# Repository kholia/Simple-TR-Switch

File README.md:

### Simple-TR-Switch

This is a non-RF-sensing, MCU PTT-controlled `Simple T/R Switch` with RX
Grounding feature which can be built for less than 2 dollars!

It was designed, and tested for https://github.com/kholia/Easy-Transceiver project.

#### Various approaches

TX power is 10W from IC-705 operating in FM mode.

- With a 2-channel relay as a T/R switch, when both RX Ground and Center are
  disconnected and left floating, a voltage of around ~2.2v is induced across
  RX connections which is unsafe for typical SDRs.

  ~2.2 Vpp is 10.93 dBm!

  https://www.random-science-tools.com/electronics/dBm-Watts-volts.htm

- With a 1-channel relay as a T/R switch which is switching the `Center`
  connection only, and with all Grounds (TX, RX, Antenna) shorted, a voltage of
  around ~1.66v is induced across RX connections which is theoretically safe
  for common SDRs.

- With a 2-channel relay as a T/R switch, with all Grounds (TX, RX, Antenna)
  shorted, with `Center` switching using Channel 1, and RX Center Grounding
  using Channel 2 during TX, a voltage of around ~500mV is induced across RX
  connections which should be fine for most common SDRs.

#### Comparisons

No external 12v power is needed unlike `Easy TR Switch` from https://www.qrpkits.com/ezseries.html.

The ~4000 INR `SDR Transceiver and Receiver Switch Antenna Sharer TR Switch Box
160 MHz` from Banggood doesn't work in `Automatic Mode` if there is
`Broadcast/SW Interference` in your area. The Banggood TR switch switches on
the RTX (red) and disconnects the SDR (RX) as soon as the antenna is connected
under `BCI` conditions, when operating in `Automatic Mode`.

#### BOM

- 5V 2A DPDT OEN MICRO RELAY 46-05-2C

  - https://etstore.in/index.php/product/oen-micro-relay-5v-dpdt-46-05-2c/
  - https://www.tomsonelectronics.com/products/oen-signal-relay-5v-dpdt

#### Added Protection

Here is another additional mechanism to protect sensitive SDRs.

This is OK for HF (shortwave).

#### Alternate (but riskier) Option

Solid switching using BS170 could be another option.

The [info](./info) folder has more information on this.

#### Credits

Thanks to VU2ASH (Ashok Joshi), K.P.S. Kang, and LW1ECP (Daniel Alonso) for all
the help.

https://circuits-diy.com/optocoupler-relay-driver-with-pc817-2n3904/

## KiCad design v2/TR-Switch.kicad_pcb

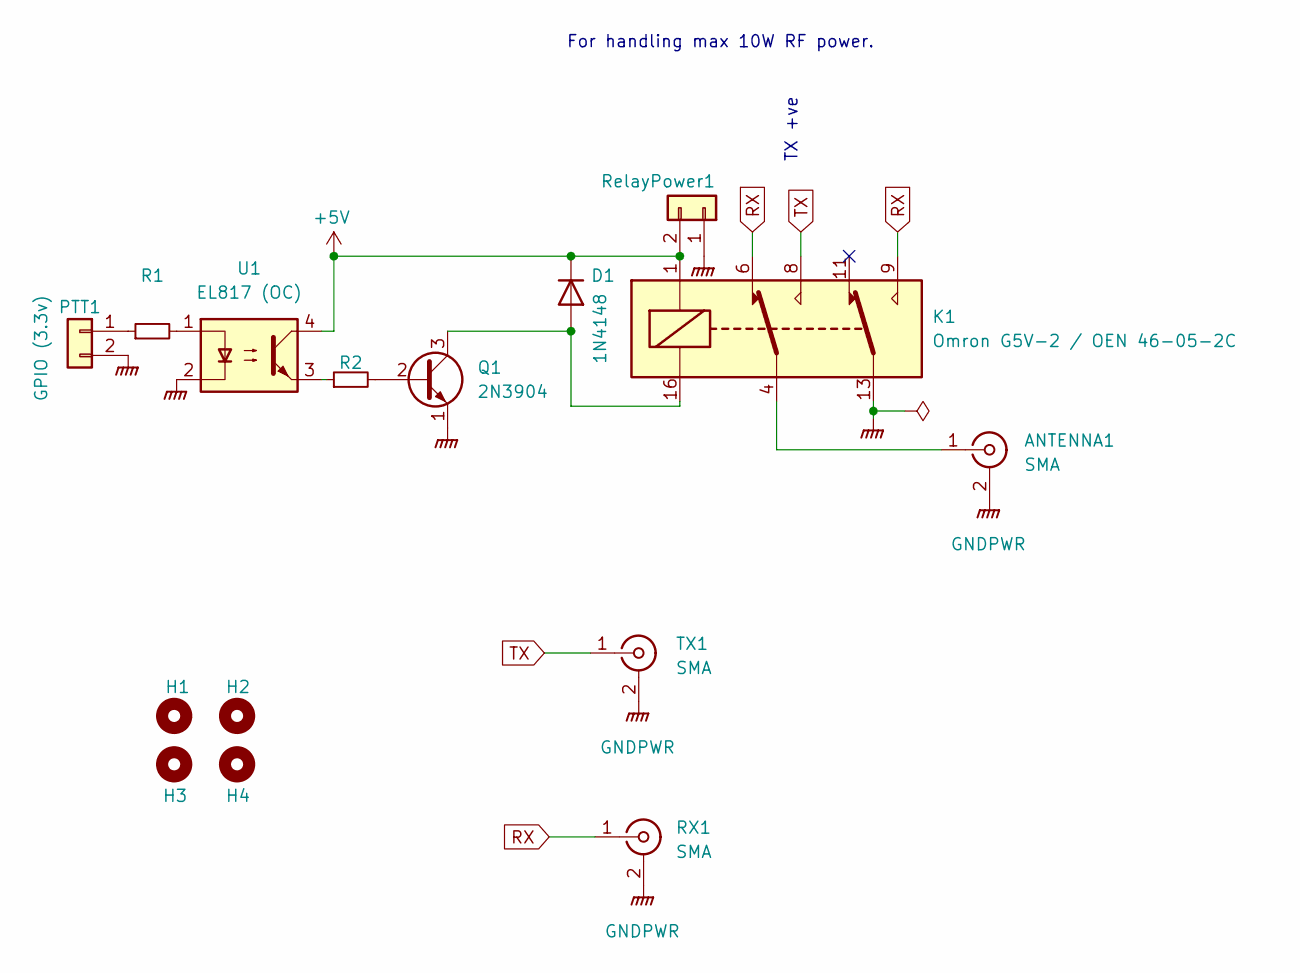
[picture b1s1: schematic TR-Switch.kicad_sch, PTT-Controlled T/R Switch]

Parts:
ANTENNA1: SMA; SMA_Amphenol_901-144_Vertical
D1: 1N4148; D_DO-35_SOD27_P2.54mm_Vertical_KathodeUp
H1, H2, H3, H4: MountingHole; MountingHole_2.2mm_M2
K1: Omron G5V-2 / OEN 46-05-2C; Relay_DPDT_Omron_G5V-2
PTT1: GPIO (3.3v); PinHeader_1x02_P2.54mm_Vertical
Q1: 2N3904; PinSocket_1x03_P2.54mm_Vertical
R1, R2: R_1206_3216Metric_Pad1.30x1.75mm_HandSolder
RELAY_POWER1: RelayPower1; PinHeader_1x02_P2.54mm_Vertical
RX1: SMA; SMA_Amphenol_901-144_Vertical
TX1: SMA; SMA_Amphenol_901-144_Vertical
U1: EL817 (OC); DIP-4_W7.62mm

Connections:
+5V: D1.1 (K), K1.1, RELAY_POWER1.2, U1.4
GNDPWR: ANTENNA1.2 (Ext), K1.13, PTT1.2, Q1.1 (E), RELAY_POWER1.1, RX1.2 (Ext), TX1.2 (Ext), U1.2
unnamed: ANTENNA1.1 (In), K1.4
unnamed: D1.2 (A), K1.16, Q1.3 (C)
unnamed: PTT1.1, R1.1
unnamed: Q1.2 (B), R2.2
unnamed: R1.2, U1.1
unnamed: R2.1, U1.3
RX: K1.6, K1.9, RX1.1 (In)
TX: K1.8, TX1.1 (In)

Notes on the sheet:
TX +ve
For handling max 10W RF power.

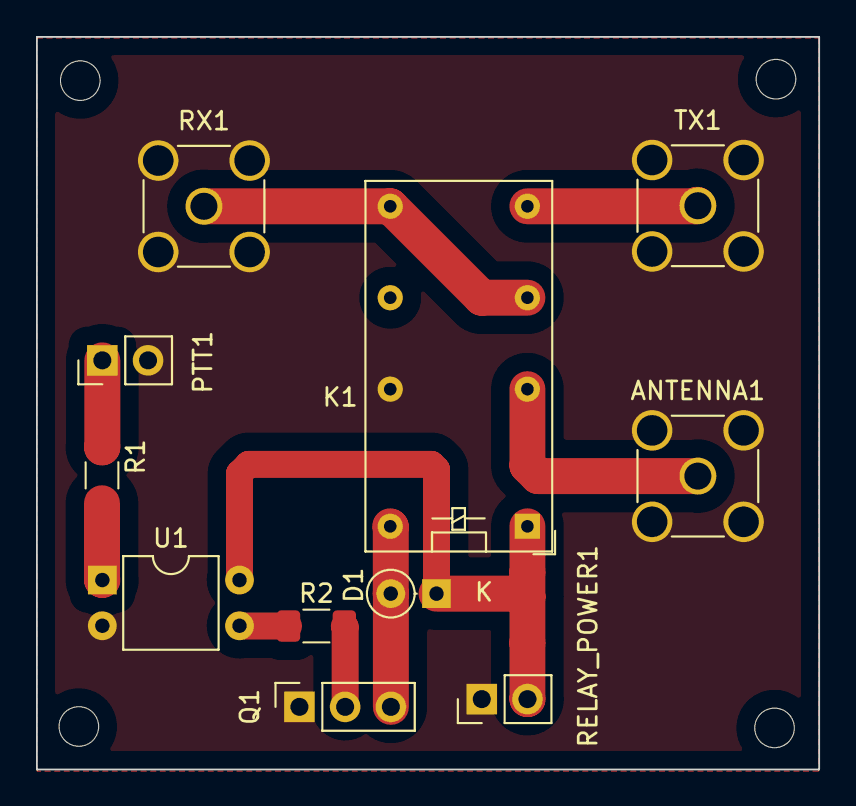
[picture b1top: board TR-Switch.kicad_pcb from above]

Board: 2 copper layers, 43.5 x 40.7 mm, 15 parts (0 on the bottom side), 10 nets.

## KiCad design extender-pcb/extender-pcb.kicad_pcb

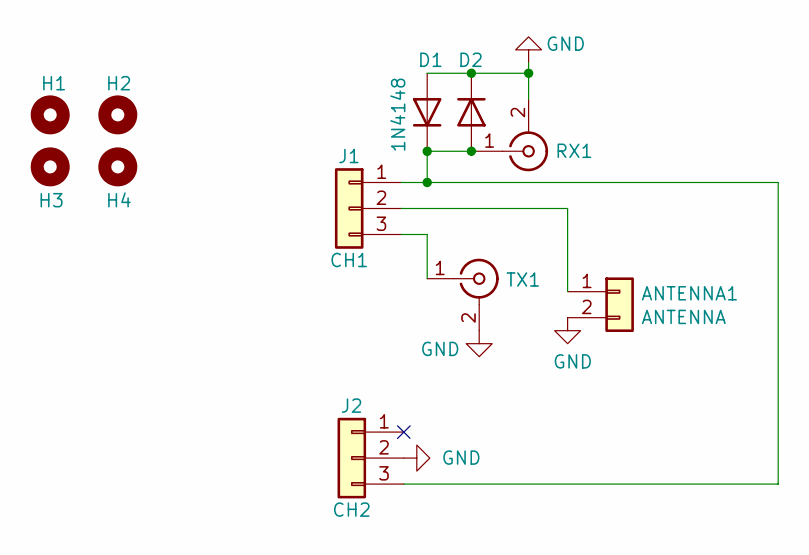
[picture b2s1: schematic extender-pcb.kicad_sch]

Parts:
ANTENNA1: ANTENNA; TerminalBlock_bornier-2_P5.08mm
D1: 1N4148; D_DO-35_SOD27_P2.54mm_Vertical_KathodeUp
D2: 1N4148; D_DO-35_SOD27_P2.54mm_Vertical_AnodeUp
H1, H2, H3, H4: MountingHole; MountingHole_2.2mm_M2
J1: CH1; TerminalBlock_bornier-3_P5.08mm
J2: CH2; TerminalBlock_bornier-3_P5.08mm
RX1: Conn_Coaxial; SMA_Amphenol_901-144_Vertical
TX1: Conn_Coaxial; SMA_Amphenol_901-144_Vertical

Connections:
GND: ANTENNA1.2, D1.2 (A), D2.1 (K), J2.2, RX1.2 (Ext), TX1.2 (Ext)
unnamed: ANTENNA1.1, J1.2
unnamed: D1.1 (K), D2.2 (A), J1.1, J2.3, RX1.1 (In)
unnamed: J1.3, TX1.1 (In)

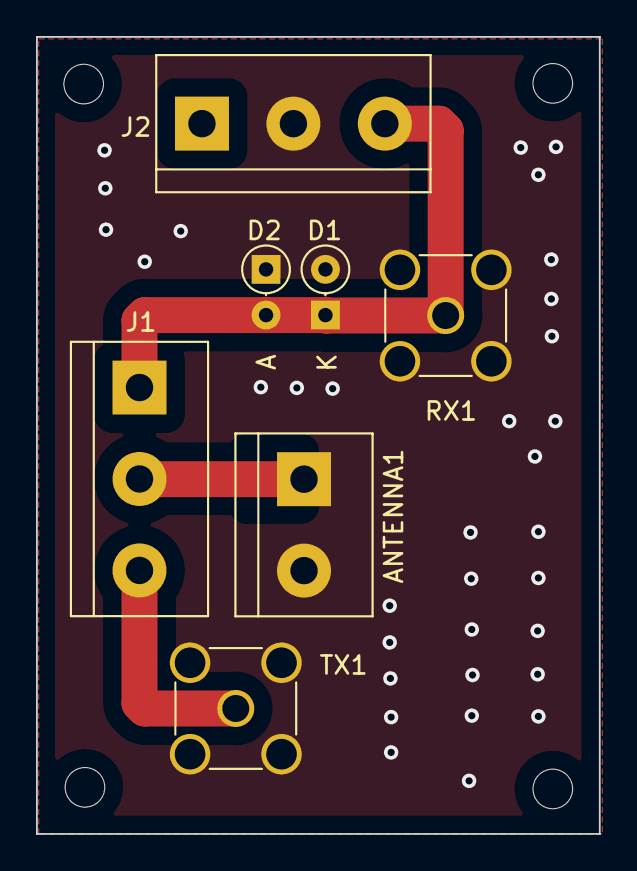
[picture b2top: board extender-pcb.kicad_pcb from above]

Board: 2 copper layers, 31.3 x 44.3 mm, 11 parts (0 on the bottom side), 4 nets.
